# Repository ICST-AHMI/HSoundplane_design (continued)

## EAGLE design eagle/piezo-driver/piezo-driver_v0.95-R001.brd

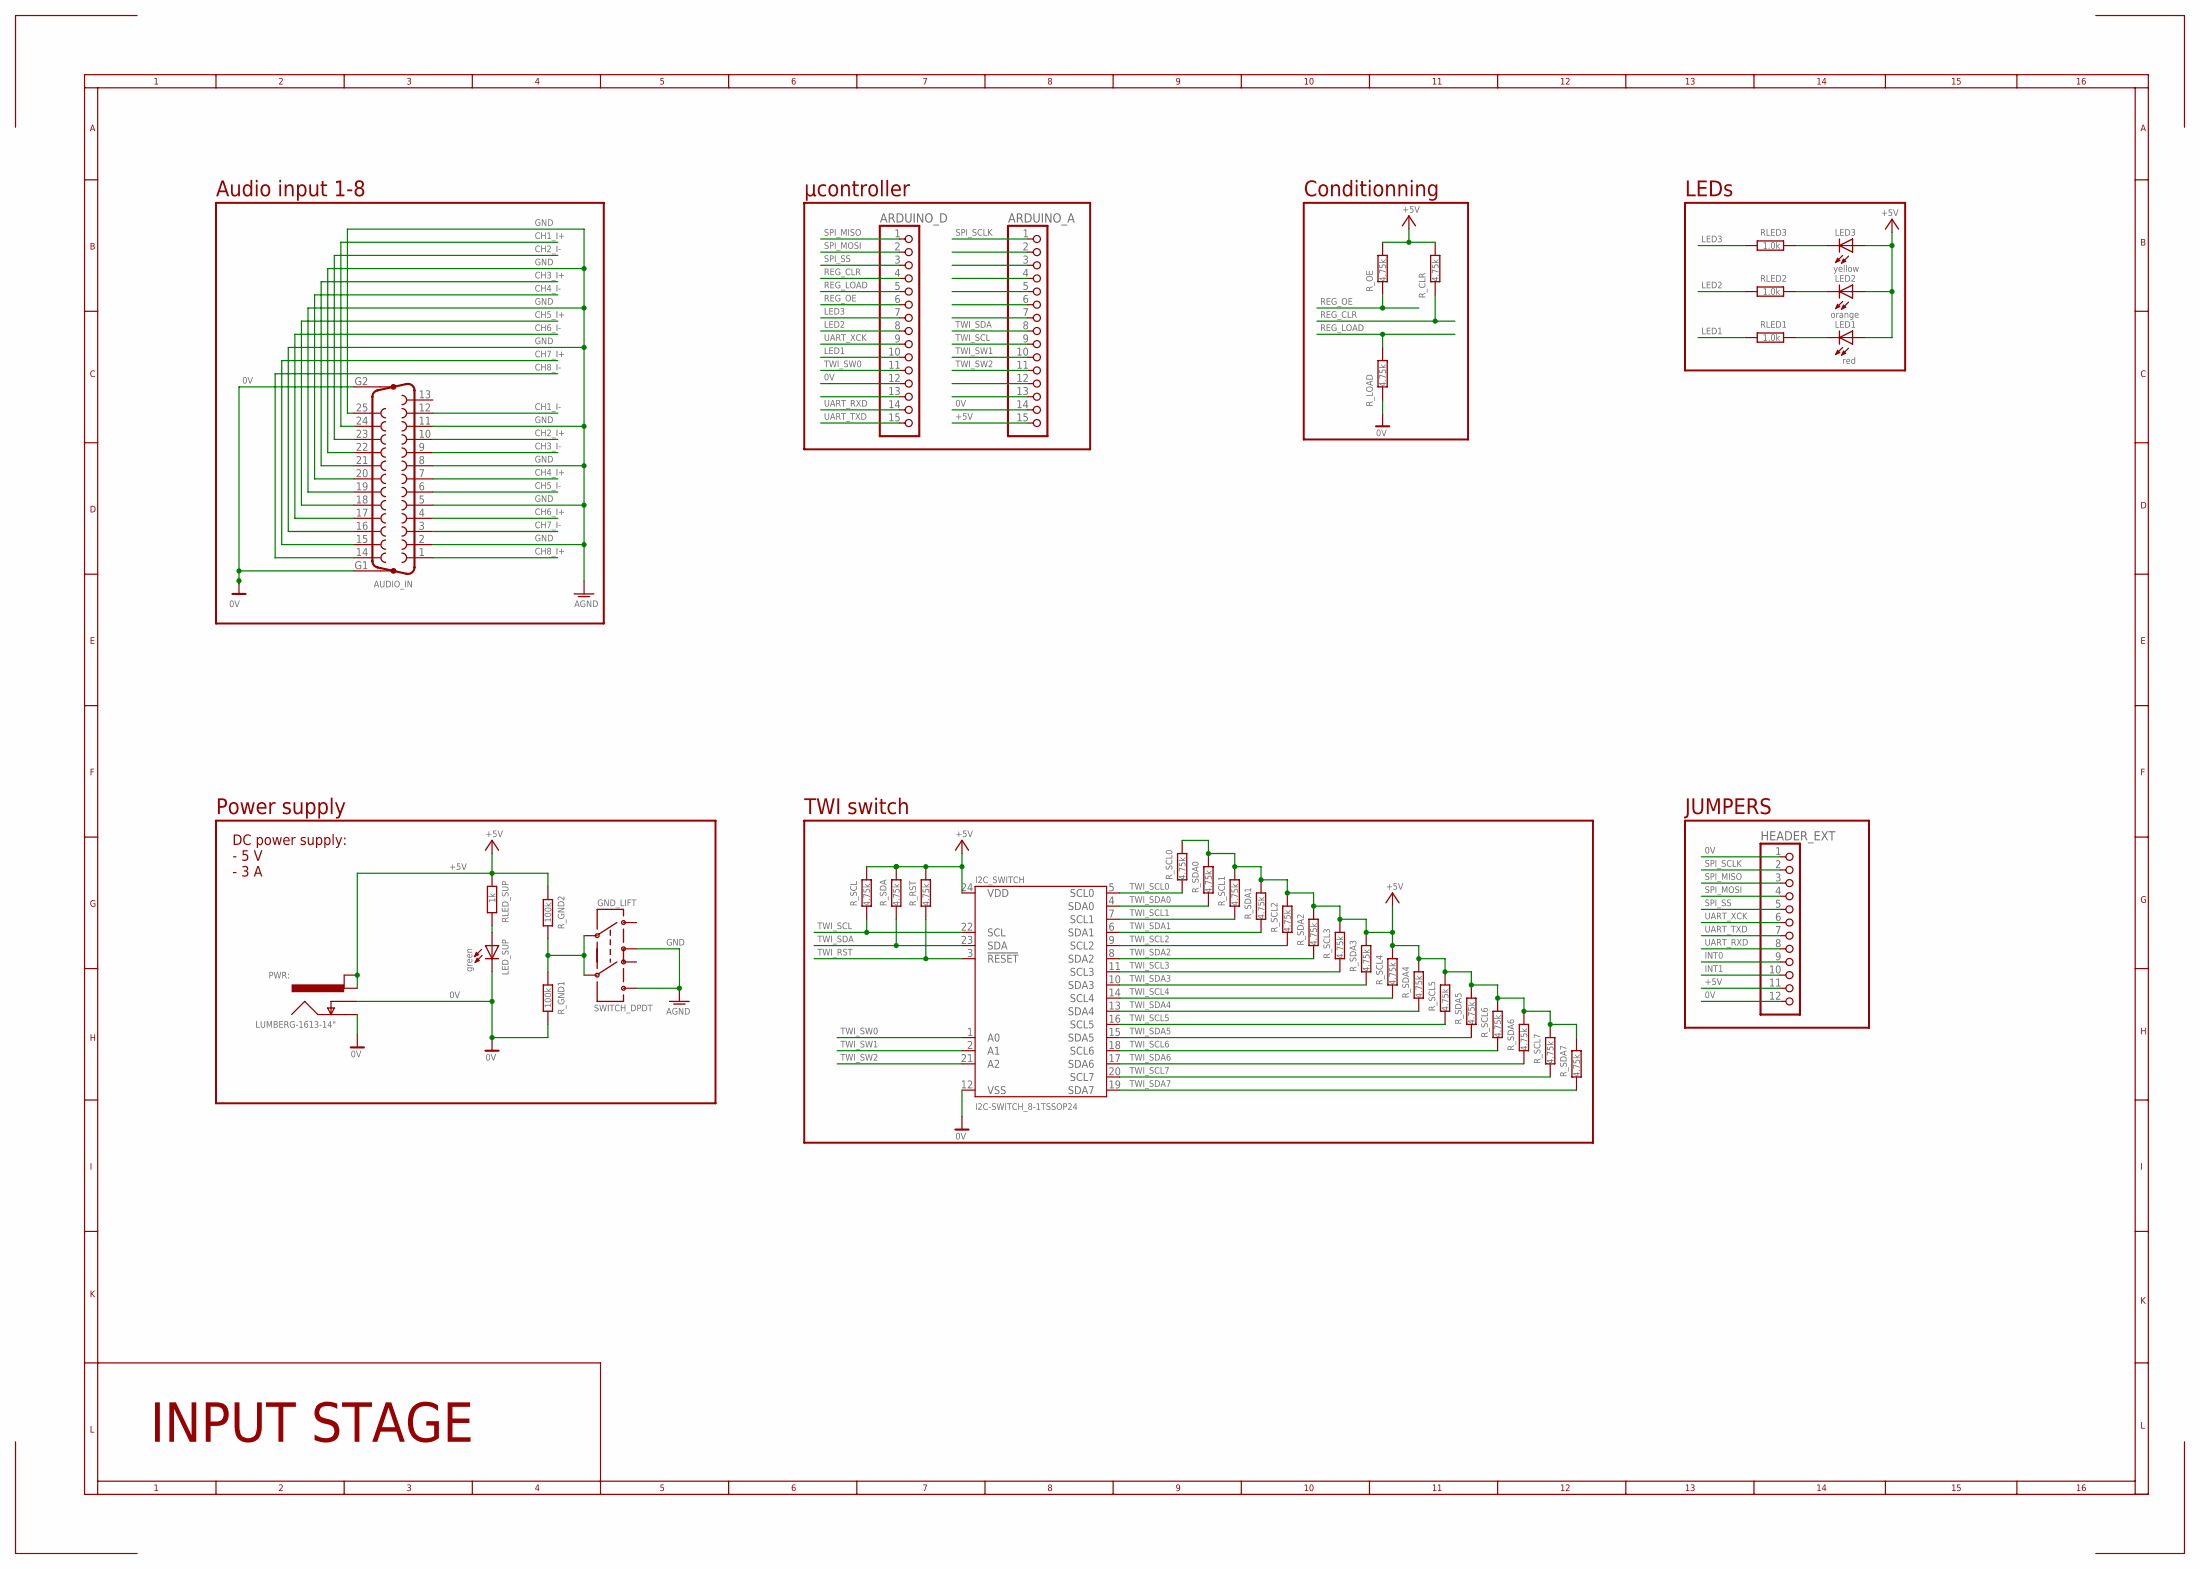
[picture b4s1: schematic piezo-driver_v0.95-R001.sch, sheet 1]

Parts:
ARDUINO_A: PINHD-1X15; 1X15
ARDUINO_D: PINHD-1X15; 1X15
AUDIO_IN: F25HP
GND_LIFT: SWITCH_DPDT; SWITCH_JS202011
HEADER_EXT: PINHD-1X12; 1X12
I2C_SWITCH: I2C-SWITCH_8-1TSSOP24; TSSOP24
LED1: red; LED-1206
LED2: orange; LED-1206
LED3: yellow; LED-1206
LED_SUP: green; LED-1206
PWR:: LUMBERG-1613-14"; LUMBERG-1613_14
RLED1, RLED2, RLED3: 1.0k; R0402
RLED_SUP: 1k; R0402
R_CLR: 4.75k; R0402
R_GND1, R_GND2: 100k; R0402
R_LOAD: 4.75k; R0402
R_OE: 4.75k; R0402
R_RST: 4.75k; R0402
R_SCL, R_SCL0, R_SCL1, R_SCL2, R_SCL3, R_SCL4, R_SCL5, R_SCL6, R_SCL7: 4.75k; R0402
R_SDA, R_SDA0, R_SDA1, R_SDA2, R_SDA3, R_SDA4, R_SDA5, R_SDA6, R_SDA7: 4.75k; R0402

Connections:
0V: ARDUINO_A.14, ARDUINO_D.12, AUDIO_IN.G1, AUDIO_IN.G2, HEADER_EXT.1, HEADER_EXT.12, I2C_SWITCH.12 (VSS), LED_SUP.C, PWR:.1 (GND), PWR:.2 (GND_INS), R_GND1.1, R_LOAD.1; also elsewhere on the board
+5V: ARDUINO_A.15, HEADER_EXT.11, I2C_SWITCH.24 (VDD), LED1.A, LED2.A, LED3.A, PWR:.3 (PWR_1), PWR:.4 (PWR_2), RLED_SUP.2, R_CLR.2, R_GND2.2, R_OE.2, R_RST.2, R_SCL.2, R_SCL0.2, R_SCL1.2, R_SCL2.2, R_SCL3.2, R_SCL4.2, R_SCL5.2, R_SCL6.2, R_SCL7.2, R_SDA.2, R_SDA0.2, R_SDA1.2, R_SDA2.2, R_SDA3.2, R_SDA4.2, R_SDA5.2, R_SDA6.2, R_SDA7.2; also elsewhere on the board
A_3V3: ARDUINO_A.2
A_5V: ARDUINO_A.12
A_A0: ARDUINO_A.4
A_A1: ARDUINO_A.5
A_A2: ARDUINO_A.6
A_A3: ARDUINO_A.7
A_REF: ARDUINO_A.3
A_RST1: ARDUINO_D.13
A_RST2: ARDUINO_A.13
CH1_I+: AUDIO_IN.24; also elsewhere on the board
CH1_I-: AUDIO_IN.12; also elsewhere on the board
CH2_I+: AUDIO_IN.10; also elsewhere on the board
CH2_I-: AUDIO_IN.23; also elsewhere on the board
CH3_I+: AUDIO_IN.21; also elsewhere on the board
CH3_I-: AUDIO_IN.9; also elsewhere on the board
CH4_I+: AUDIO_IN.7; also elsewhere on the board
CH4_I-: AUDIO_IN.20; also elsewhere on the board
CH5_I+: AUDIO_IN.18; also elsewhere on the board
CH5_I-: AUDIO_IN.6; also elsewhere on the board
CH6_I+: AUDIO_IN.4; also elsewhere on the board
CH6_I-: AUDIO_IN.17; also elsewhere on the board
CH7_I+: AUDIO_IN.15; also elsewhere on the board
CH7_I-: AUDIO_IN.3; also elsewhere on the board
CH8_I+: AUDIO_IN.1; also elsewhere on the board
CH8_I-: AUDIO_IN.14; also elsewhere on the board
GND: AUDIO_IN.2, AUDIO_IN.5, AUDIO_IN.8, AUDIO_IN.11, AUDIO_IN.16, AUDIO_IN.19, AUDIO_IN.22, AUDIO_IN.25, GND_LIFT.1 (T1A), GND_LIFT.6 (T2A)
INT0: HEADER_EXT.9
INT1: HEADER_EXT.10
LED1: ARDUINO_D.10, RLED1.1
LED2: ARDUINO_D.8, RLED2.1
LED3: ARDUINO_D.7, RLED3.1
unnamed: LED_SUP.A, RLED_SUP.1
unnamed: LED3.C, RLED3.2
unnamed: LED2.C, RLED2.2
unnamed: LED1.C, RLED1.2
unnamed: GND_LIFT.2 (P1), GND_LIFT.5 (P2), R_GND1.2, R_GND2.1
REG_CLR: ARDUINO_D.4, R_CLR.1; also elsewhere on the board
REG_LOAD: ARDUINO_D.5, R_LOAD.2; also elsewhere on the board
REG_OE: ARDUINO_D.6, R_OE.1; also elsewhere on the board
SPI_MISO: ARDUINO_D.1, HEADER_EXT.3
SPI_MOSI: ARDUINO_D.2, HEADER_EXT.4; also elsewhere on the board
SPI_SCLK: ARDUINO_A.1, HEADER_EXT.2; also elsewhere on the board
SPI_SS: ARDUINO_D.3, HEADER_EXT.5
TWI_RST: I2C_SWITCH.3 (!RESET), R_RST.1
TWI_SCL: ARDUINO_A.9, I2C_SWITCH.22 (SCL), R_SCL.1
TWI_SCL0: I2C_SWITCH.5 (SCL0), R_SCL0.1; also elsewhere on the board
TWI_SCL1: I2C_SWITCH.7 (SCL1), R_SCL1.1; also elsewhere on the board
TWI_SCL2: I2C_SWITCH.9 (SCL2), R_SCL2.1; also elsewhere on the board
TWI_SCL3: I2C_SWITCH.11 (SCL3), R_SCL3.1; also elsewhere on the board
TWI_SCL4: I2C_SWITCH.14 (SCL4), R_SCL4.1; also elsewhere on the board
TWI_SCL5: I2C_SWITCH.16 (SCL5), R_SCL5.1; also elsewhere on the board
TWI_SCL6: I2C_SWITCH.18 (SCL6), R_SCL6.1; also elsewhere on the board
TWI_SCL7: I2C_SWITCH.20 (SCL7), R_SCL7.1; also elsewhere on the board
TWI_SDA: ARDUINO_A.8, I2C_SWITCH.23 (SDA), R_SDA.1
TWI_SDA0: I2C_SWITCH.4 (SDA0), R_SDA0.1; also elsewhere on the board
TWI_SDA1: I2C_SWITCH.6 (SDA1), R_SDA1.1; also elsewhere on the board
TWI_SDA2: I2C_SWITCH.8 (SDA2), R_SDA2.1; also elsewhere on the board
TWI_SDA3: I2C_SWITCH.10 (SDA3), R_SDA3.1; also elsewhere on the board
TWI_SDA4: I2C_SWITCH.13 (SDA4), R_SDA4.1; also elsewhere on the board
TWI_SDA5: I2C_SWITCH.15 (SDA5), R_SDA5.1; also elsewhere on the board
TWI_SDA6: I2C_SWITCH.17 (SDA6), R_SDA6.1; also elsewhere on the board
TWI_SDA7: I2C_SWITCH.19 (SDA7), R_SDA7.1; also elsewhere on the board
TWI_SW0: ARDUINO_D.11, I2C_SWITCH.1 (A0)
TWI_SW1: ARDUINO_A.10, I2C_SWITCH.2 (A1)
TWI_SW2: ARDUINO_A.11, I2C_SWITCH.21 (A2)
UART_RXD: ARDUINO_D.14, HEADER_EXT.8
UART_TXD: ARDUINO_D.15, HEADER_EXT.7
UART_XCK: ARDUINO_D.9, HEADER_EXT.6

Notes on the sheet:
Audio input 1-8
Power supply
DC power supply: - 5 V - 3 A
INPUT STAGE
µcontroller
LEDs
JUMPERS
TWI switch
Conditionning

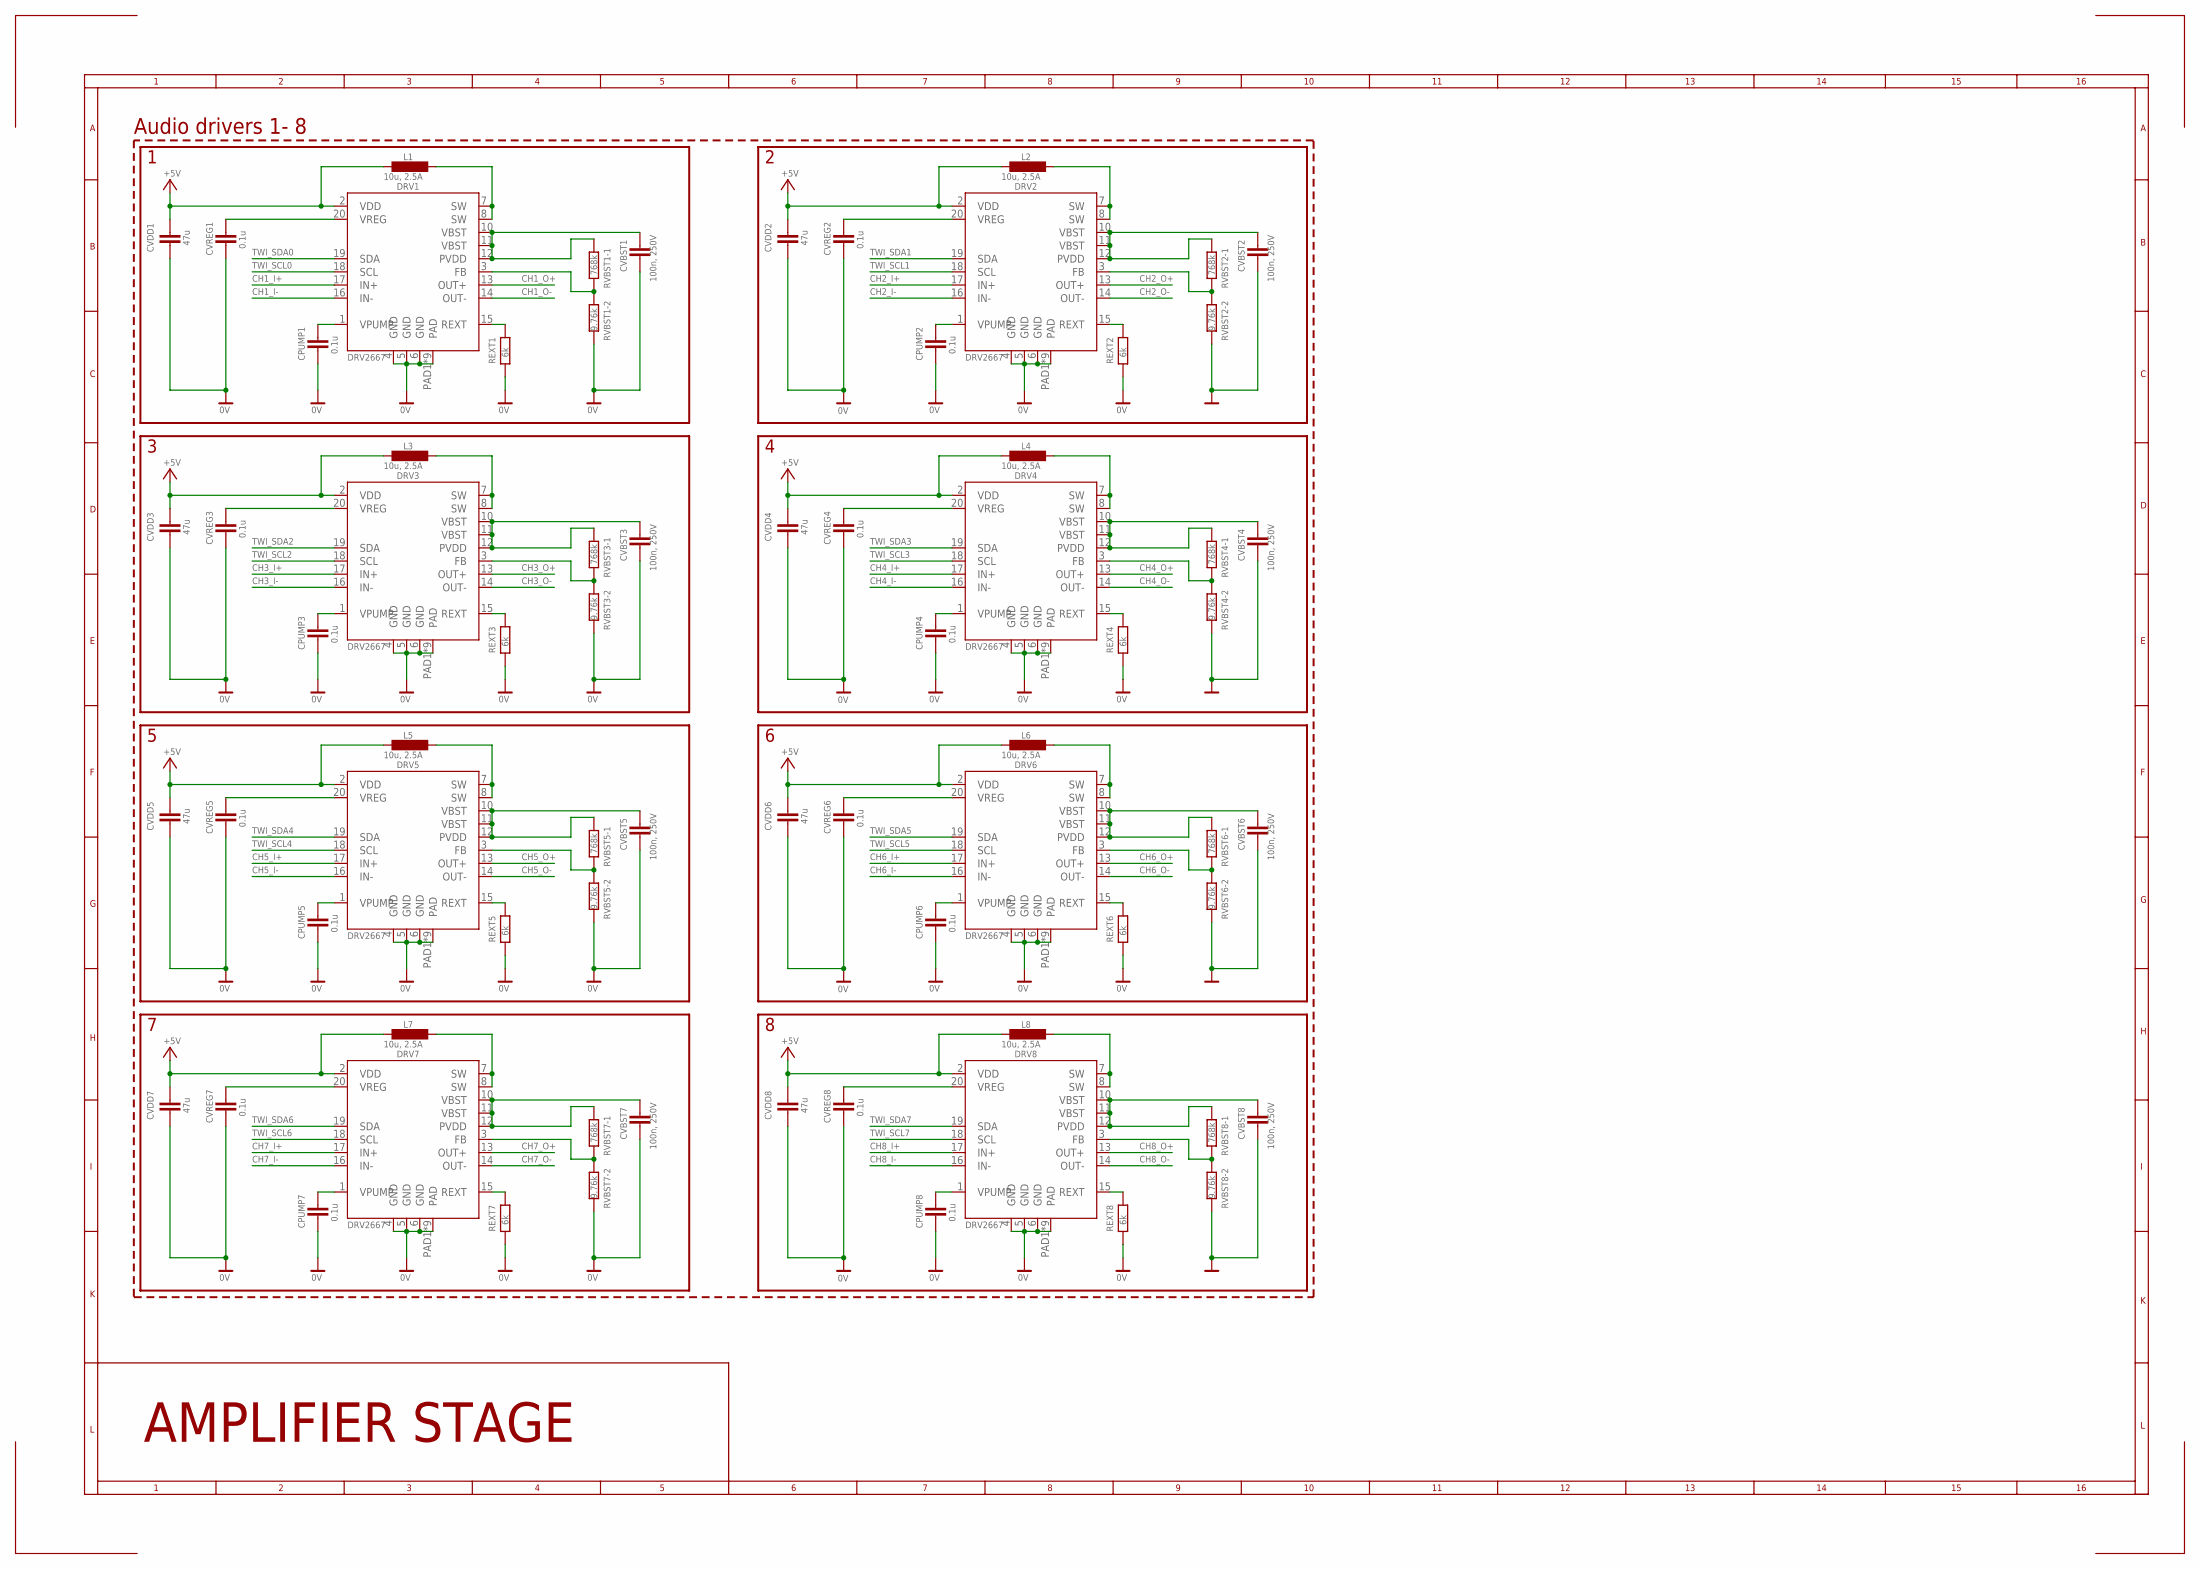
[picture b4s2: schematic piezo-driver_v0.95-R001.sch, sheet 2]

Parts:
CPUMP1, CPUMP2, CPUMP3, CPUMP4, CPUMP5, CPUMP6, CPUMP7, CPUMP8: 0.1u; C0402
CVBST1, CVBST2, CVBST3, CVBST4, CVBST5, CVBST6, CVBST7, CVBST8: 100n, 250V; C0805
CVDD1, CVDD2, CVDD3, CVDD4, CVDD5, CVDD6, CVDD7, CVDD8: 47u; C0402
CVREG1, CVREG2, CVREG3, CVREG4, CVREG5, CVREG6, CVREG7, CVREG8: 0.1u; C0402
DRV1, DRV2, DRV3, DRV4, DRV5, DRV6, DRV7, DRV8: DRV2667; QFN-20_9TH
L1, L2, L3, L4, L5, L6, L7, L8: 10u, 2.5A; L3030
REXT1, REXT2, REXT3, REXT4, REXT5, REXT6, REXT7, REXT8: 6k; R0402
RVBST1-1, RVBST2-1, RVBST3-1, RVBST4-1, RVBST5-1, RVBST6-1, RVBST7-1, RVBST8-1: 768k; R0402
RVBST1-2, RVBST2-2, RVBST3-2, RVBST4-2, RVBST5-2, RVBST6-2, RVBST7-2, RVBST8-2: 9.76k; R0402

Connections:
0V: CPUMP1.2, CPUMP2.2, CPUMP3.2, CPUMP4.2, CPUMP5.2, CPUMP6.2, CPUMP7.2, CPUMP8.2, CVBST1.2, CVBST2.2, CVBST3.2, CVBST4.2, CVBST5.2, CVBST6.2, CVBST7.2, CVBST8.2, CVDD1.2, CVDD2.2, CVDD3.2, CVDD4.2, CVDD5.2, CVDD6.2, CVDD7.2, CVDD8.2, CVREG1.2, CVREG2.2, CVREG3.2, CVREG4.2, CVREG5.2, CVREG6.2, CVREG7.2, CVREG8.2, DRV1.4 (GND), DRV1.5 (GND), DRV1.6 (GND), DRV1.PAD1 (PAD), DRV1.PAD2 (PAD), DRV1.PAD3 (PAD), DRV1.PAD4 (PAD), DRV1.PAD5 (PAD), DRV1.PAD6 (PAD), DRV1.PAD7 (PAD), DRV1.PAD8 (PAD), DRV1.PAD9 (PAD), DRV2.4 (GND), DRV2.5 (GND), DRV2.6 (GND), DRV2.PAD1 (PAD), DRV2.PAD2 (PAD), DRV2.PAD3 (PAD), DRV2.PAD4 (PAD), DRV2.PAD5 (PAD), DRV2.PAD6 (PAD), DRV2.PAD7 (PAD), DRV2.PAD8 (PAD), DRV2.PAD9 (PAD), DRV3.4 (GND), DRV3.5 (GND), DRV3.6 (GND), DRV3.PAD1 (PAD), DRV3.PAD2 (PAD), DRV3.PAD3 (PAD), DRV3.PAD4 (PAD), DRV3.PAD5 (PAD), DRV3.PAD6 (PAD), DRV3.PAD7 (PAD), DRV3.PAD8 (PAD), DRV3.PAD9 (PAD), DRV4.4 (GND), DRV4.5 (GND), DRV4.6 (GND), DRV4.PAD1 (PAD), DRV4.PAD2 (PAD), DRV4.PAD3 (PAD), DRV4.PAD4 (PAD), DRV4.PAD5 (PAD), DRV4.PAD6 (PAD), DRV4.PAD7 (PAD), DRV4.PAD8 (PAD), DRV4.PAD9 (PAD), DRV5.4 (GND), DRV5.5 (GND), DRV5.6 (GND), DRV5.PAD1 (PAD), DRV5.PAD2 (PAD), DRV5.PAD3 (PAD), DRV5.PAD4 (PAD), DRV5.PAD5 (PAD), DRV5.PAD6 (PAD), DRV5.PAD7 (PAD), DRV5.PAD8 (PAD), DRV5.PAD9 (PAD), DRV6.4 (GND), DRV6.5 (GND), DRV6.6 (GND), DRV6.PAD1 (PAD), DRV6.PAD2 (PAD), DRV6.PAD3 (PAD), DRV6.PAD4 (PAD), DRV6.PAD5 (PAD), DRV6.PAD6 (PAD), DRV6.PAD7 (PAD), DRV6.PAD8 (PAD), DRV6.PAD9 (PAD), DRV7.4 (GND), DRV7.5 (GND), DRV7.6 (GND), DRV7.PAD1 (PAD), DRV7.PAD2 (PAD), DRV7.PAD3 (PAD), DRV7.PAD4 (PAD), DRV7.PAD5 (PAD), DRV7.PAD6 (PAD), DRV7.PAD7 (PAD), DRV7.PAD8 (PAD), DRV7.PAD9 (PAD), DRV8.4 (GND), DRV8.5 (GND), DRV8.6 (GND), DRV8.PAD1 (PAD), DRV8.PAD2 (PAD), DRV8.PAD3 (PAD), DRV8.PAD4 (PAD), DRV8.PAD5 (PAD), DRV8.PAD6 (PAD), DRV8.PAD7 (PAD), DRV8.PAD8 (PAD), DRV8.PAD9 (PAD), REXT1.1, REXT2.1, REXT3.1, REXT4.1, REXT5.1, REXT6.1, REXT7.1, REXT8.1, RVBST1-2.1, RVBST2-2.1, RVBST3-2.1, RVBST4-2.1, RVBST5-2.1, RVBST6-2.1, RVBST7-2.1, RVBST8-2.1; also elsewhere on the board
+5V: CVDD1.1, CVDD2.1, CVDD3.1, CVDD4.1, CVDD5.1, CVDD6.1, CVDD7.1, CVDD8.1, DRV1.2 (VDD), DRV2.2 (VDD), DRV3.2 (VDD), DRV4.2 (VDD), DRV5.2 (VDD), DRV6.2 (VDD), DRV7.2 (VDD), DRV8.2 (VDD), L1.2, L2.2, L3.2, L4.2, L5.2, L6.2, L7.2, L8.2; also elsewhere on the board
CH1_I+: DRV1.17 (IN+); also elsewhere on the board
CH1_I-: DRV1.16 (IN-); also elsewhere on the board
CH1_O+: DRV1.13 (OUT+); also elsewhere on the board
CH1_O-: DRV1.14 (OUT-); also elsewhere on the board
CH2_I+: DRV2.17 (IN+); also elsewhere on the board
CH2_I-: DRV2.16 (IN-); also elsewhere on the board
CH2_O+: DRV2.13 (OUT+); also elsewhere on the board
CH2_O-: DRV2.14 (OUT-); also elsewhere on the board
CH3_I+: DRV3.17 (IN+); also elsewhere on the board
CH3_I-: DRV3.16 (IN-); also elsewhere on the board
CH3_O+: DRV3.13 (OUT+); also elsewhere on the board
CH3_O-: DRV3.14 (OUT-); also elsewhere on the board
CH4_I+: DRV4.17 (IN+); also elsewhere on the board
CH4_I-: DRV4.16 (IN-); also elsewhere on the board
CH4_O+: DRV4.13 (OUT+); also elsewhere on the board
CH4_O-: DRV4.14 (OUT-); also elsewhere on the board
CH5_I+: DRV5.17 (IN+); also elsewhere on the board
CH5_I-: DRV5.16 (IN-); also elsewhere on the board
CH5_O+: DRV5.13 (OUT+); also elsewhere on the board
CH5_O-: DRV5.14 (OUT-); also elsewhere on the board
CH6_I+: DRV6.17 (IN+); also elsewhere on the board
CH6_I-: DRV6.16 (IN-); also elsewhere on the board
CH6_O+: DRV6.13 (OUT+); also elsewhere on the board
CH6_O-: DRV6.14 (OUT-); also elsewhere on the board
CH7_I+: DRV7.17 (IN+); also elsewhere on the board
CH7_I-: DRV7.16 (IN-); also elsewhere on the board
CH7_O+: DRV7.13 (OUT+); also elsewhere on the board
CH7_O-: DRV7.14 (OUT-); also elsewhere on the board
CH8_I+: DRV8.17 (IN+); also elsewhere on the board
CH8_I-: DRV8.16 (IN-); also elsewhere on the board
CH8_O+: DRV8.13 (OUT+); also elsewhere on the board
CH8_O-: DRV8.14 (OUT-); also elsewhere on the board
CVBST1: CVBST1.1, DRV1.10 (VBST), DRV1.11 (VBST), DRV1.12 (PVDD), RVBST1-1.2
CVBST2: CVBST2.1, DRV2.10 (VBST), DRV2.11 (VBST), DRV2.12 (PVDD), RVBST2-1.2
CVBST3: CVBST3.1, DRV3.10 (VBST), DRV3.11 (VBST), DRV3.12 (PVDD), RVBST3-1.2
CVBST4: CVBST4.1, DRV4.10 (VBST), DRV4.11 (VBST), DRV4.12 (PVDD), RVBST4-1.2
CVBST5: CVBST5.1, DRV5.10 (VBST), DRV5.11 (VBST), DRV5.12 (PVDD), RVBST5-1.2
CVBST6: CVBST6.1, DRV6.10 (VBST), DRV6.11 (VBST), DRV6.12 (PVDD), RVBST6-1.2
CVBST7: CVBST7.1, DRV7.10 (VBST), DRV7.11 (VBST), DRV7.12 (PVDD), RVBST7-1.2
CVBST8: CVBST8.1, DRV8.10 (VBST), DRV8.11 (VBST), DRV8.12 (PVDD), RVBST8-1.2
L1: DRV1.7 (SW), DRV1.8 (SW), L1.1
L2: DRV2.7 (SW), DRV2.8 (SW), L2.1
L3: DRV3.7 (SW), DRV3.8 (SW), L3.1
L4: DRV4.7 (SW), DRV4.8 (SW), L4.1
L5: DRV5.7 (SW), DRV5.8 (SW), L5.1
L6: DRV6.7 (SW), DRV6.8 (SW), L6.1
L7: DRV7.7 (SW), DRV7.8 (SW), L7.1
L8: DRV8.7 (SW), DRV8.8 (SW), L8.1
unnamed: DRV1.3 (FB), RVBST1-1.1, RVBST1-2.2
unnamed: DRV1.15 (REXT), REXT1.2
unnamed: CPUMP1.1, DRV1.1 (VPUMP)
unnamed: CVREG1.1, DRV1.20 (VREG)
unnamed: DRV3.3 (FB), RVBST3-1.1, RVBST3-2.2
unnamed: DRV3.15 (REXT), REXT3.2
unnamed: CPUMP3.1, DRV3.1 (VPUMP)
unnamed: CVREG3.1, DRV3.20 (VREG)
unnamed: DRV4.3 (FB), RVBST4-1.1, RVBST4-2.2
unnamed: DRV4.15 (REXT), REXT4.2
unnamed: CPUMP4.1, DRV4.1 (VPUMP)
unnamed: CVREG4.1, DRV4.20 (VREG)
unnamed: DRV2.3 (FB), RVBST2-1.1, RVBST2-2.2
unnamed: DRV2.15 (REXT), REXT2.2
unnamed: CPUMP2.1, DRV2.1 (VPUMP)
unnamed: CVREG2.1, DRV2.20 (VREG)
unnamed: DRV5.3 (FB), RVBST5-1.1, RVBST5-2.2
unnamed: DRV5.15 (REXT), REXT5.2
unnamed: CPUMP5.1, DRV5.1 (VPUMP)
unnamed: CVREG5.1, DRV5.20 (VREG)
unnamed: DRV6.3 (FB), RVBST6-1.1, RVBST6-2.2
unnamed: DRV6.15 (REXT), REXT6.2
unnamed: CPUMP6.1, DRV6.1 (VPUMP)
unnamed: CVREG6.1, DRV6.20 (VREG)
unnamed: DRV7.3 (FB), RVBST7-1.1, RVBST7-2.2
unnamed: DRV7.15 (REXT), REXT7.2
unnamed: CPUMP7.1, DRV7.1 (VPUMP)
unnamed: CVREG7.1, DRV7.20 (VREG)
unnamed: DRV8.3 (FB), RVBST8-1.1, RVBST8-2.2
unnamed: DRV8.15 (REXT), REXT8.2
unnamed: CPUMP8.1, DRV8.1 (VPUMP)
unnamed: CVREG8.1, DRV8.20 (VREG)
TWI_SCL0: DRV1.18 (SCL); also elsewhere on the board
TWI_SCL1: DRV2.18 (SCL); also elsewhere on the board
TWI_SCL2: DRV3.18 (SCL); also elsewhere on the board
TWI_SCL3: DRV4.18 (SCL); also elsewhere on the board
TWI_SCL4: DRV5.18 (SCL); also elsewhere on the board
TWI_SCL5: DRV6.18 (SCL); also elsewhere on the board
TWI_SCL6: DRV7.18 (SCL); also elsewhere on the board
TWI_SCL7: DRV8.18 (SCL); also elsewhere on the board
TWI_SDA0: DRV1.19 (SDA); also elsewhere on the board
TWI_SDA1: DRV2.19 (SDA); also elsewhere on the board
TWI_SDA2: DRV3.19 (SDA); also elsewhere on the board
TWI_SDA3: DRV4.19 (SDA); also elsewhere on the board
TWI_SDA4: DRV5.19 (SDA); also elsewhere on the board
TWI_SDA5: DRV6.19 (SDA); also elsewhere on the board
TWI_SDA6: DRV7.19 (SDA); also elsewhere on the board
TWI_SDA7: DRV8.19 (SDA); also elsewhere on the board

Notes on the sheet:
AMPLIFIER STAGE
Audio drivers 1- 8
